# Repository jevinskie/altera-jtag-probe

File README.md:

# altera-jtag-probe
Adapter designed to sniff an Altera-style JTAG connection with a breakout for Saleae Loggic Pro 8

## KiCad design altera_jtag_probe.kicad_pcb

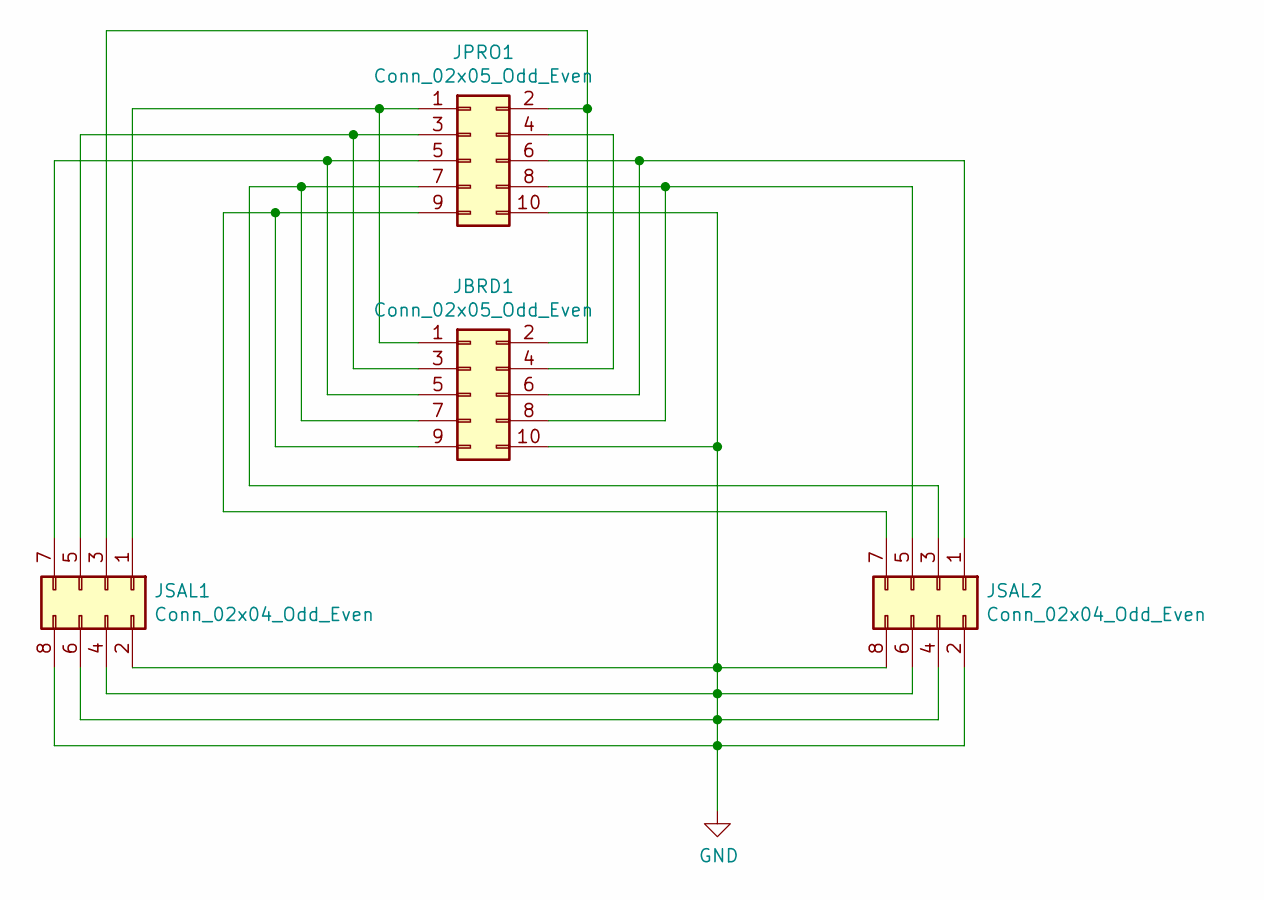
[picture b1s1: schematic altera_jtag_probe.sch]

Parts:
JBRD1: Conn_02x05_Odd_Even; PinSocket_2x05_P2.54mm_Vertical
JPRO1: Conn_02x05_Odd_Even; PinHeader_2x05_P2.54mm_Vertical
JSAL1, JSAL2: Conn_02x04_Odd_Even; PinHeader_2x04_P2.54mm_Vertical

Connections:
GND: JBRD1.10, JPRO1.10, JSAL1.2, JSAL1.4, JSAL1.6, JSAL1.8, JSAL2.2, JSAL2.4, JSAL2.6, JSAL2.8
unnamed: JBRD1.1, JPRO1.1, JSAL1.1
unnamed: JBRD1.2, JPRO1.2, JSAL1.3
unnamed: JBRD1.3, JPRO1.3, JSAL1.5
unnamed: JBRD1.4, JPRO1.4
unnamed: JBRD1.5, JPRO1.5, JSAL1.7
unnamed: JBRD1.6, JPRO1.6, JSAL2.1
unnamed: JBRD1.7, JPRO1.7, JSAL2.3
unnamed: JBRD1.8, JPRO1.8, JSAL2.5
unnamed: JBRD1.9, JPRO1.9, JSAL2.7

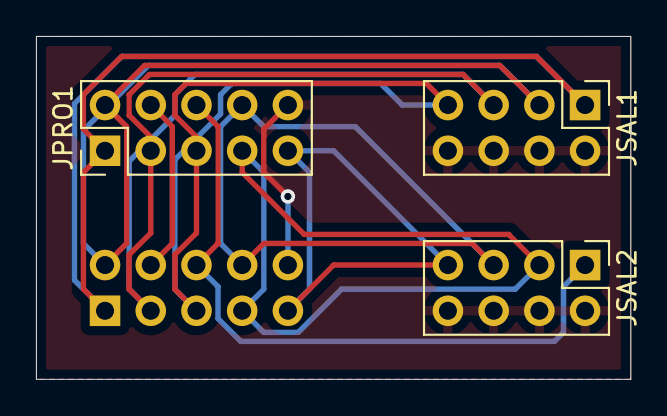
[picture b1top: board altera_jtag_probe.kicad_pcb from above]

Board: 2 copper layers, 33.0 x 19.0 mm, 4 parts (1 on the bottom side), 10 nets.

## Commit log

2021-09-05 initial commit of altera usb blaster sniffer for saleae logic pro
2021-09-08 trim size, traces are 0.3 mm instead of 0.25 mm
2022-02-15 Create LICENSE
2022-02-15 add render
